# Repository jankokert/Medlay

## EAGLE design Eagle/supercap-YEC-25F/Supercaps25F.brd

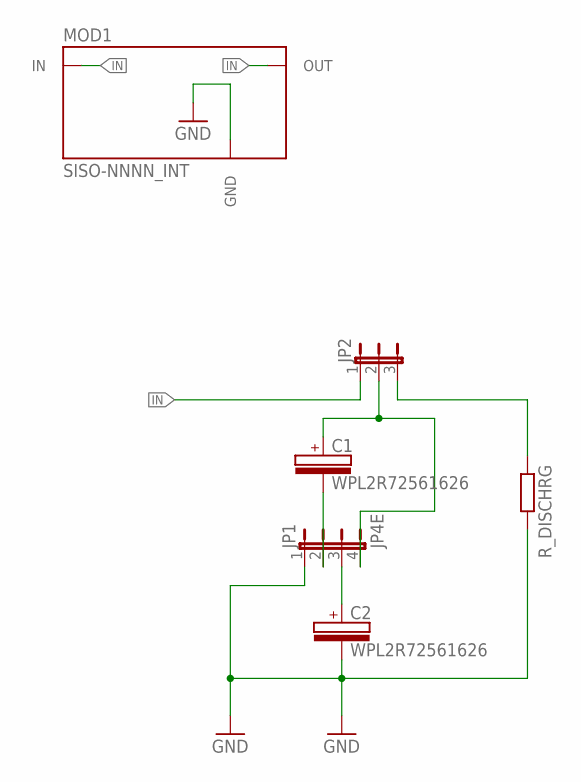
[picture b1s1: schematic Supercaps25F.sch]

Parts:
C1, C2: WPL2R72561626; DLC_16X26
JP1: JP4E; JP4
JP2: JP2E; JP2
MOD1: SISO-NNNN_INT; SISO-NNNN
R_DISCHRG: R_THROUGH-HOLE

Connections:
GND: C2.2, JP1.1, MOD1.GND1 (GND), MOD1.GND2 (GND), MOD1.GND3 (GND), MOD1.GND4 (GND), R_DISCHRG.2
IN: JP2.1, MOD1.IN1 (IN), MOD1.IN2 (IN), MOD1.IN3 (IN), MOD1.IN4 (IN), MOD1.OUT1 (OUT), MOD1.OUT2 (OUT), MOD1.OUT3 (OUT), MOD1.OUT4 (OUT)
unnamed: C1.2, JP1.2
unnamed: C2.1, JP1.3
unnamed: C1.1, JP1.4, JP2.2
unnamed: JP2.3, R_DISCHRG.1

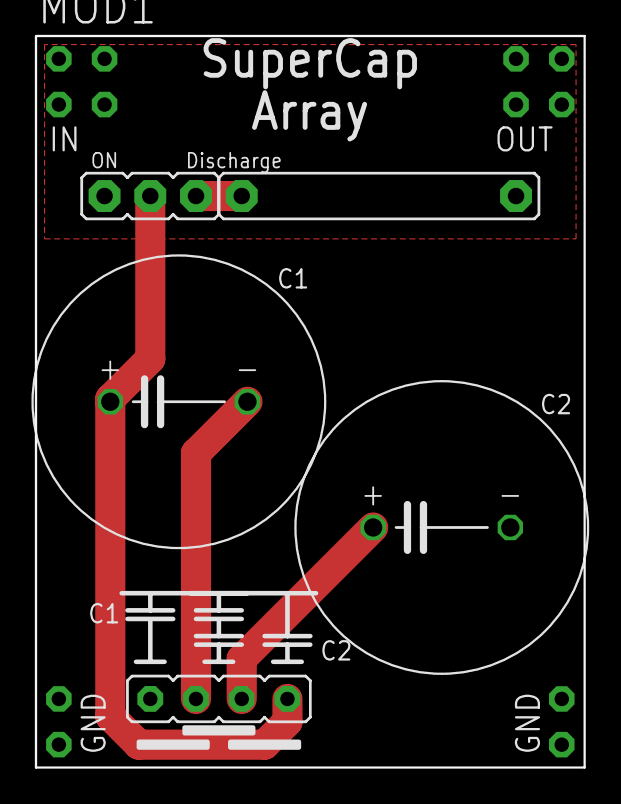
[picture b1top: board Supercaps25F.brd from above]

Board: 2 copper layers, 30.5 x 40.6 mm, 6 parts (0 on the bottom side), 6 nets.
